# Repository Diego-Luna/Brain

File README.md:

# Brain 🧠

Brain(Cerebro) es una placa de desarrollo, que cuenta con un EEG (electroencefalograma) que mediante electrodos medimos la actividad cerebral de 12 Hz - 30 Hz, que corresponde a la concentración, con el objetivo de utilizarlo como una herramienta de aprendizaje en distintas disciplinas que se puede llevar a cualquier parte para aprender mientras te diviertes.
De igual manera se está desarrollando una plataforma para facilitar el uso y el aprendizaje con Brain.

## Desarrollo de placa

Este desarollo es una colaboracion con Electronic cats ([web](https://electroniccats.com))  y MoonMakers ([web](https://moonmakers.org/)) fue creada en la plataforma de Kicad 5.1

Usamos el microcontrolador nrf52840 en la forma E73-2G4M08S1C, está construido alrededor de la CPU ARM® Cortex ™ -M4 de 32 bits, tiene soporte de protocolo para Bluetooth 5, Bluetooth mesh, Thread, Zigbee, 802.15.4, ANT y pilas propietarias de 2.4 GHz. también tienen una resolución de 12 bits en puertos analogicos.

En la parte de los filtros EEG usamos el chip ads1294, cuenta con una resolución de 24 bits por canal, y hasta con 4 canales disponibles que pueden también usarse como un ECG (electrocardiograma)

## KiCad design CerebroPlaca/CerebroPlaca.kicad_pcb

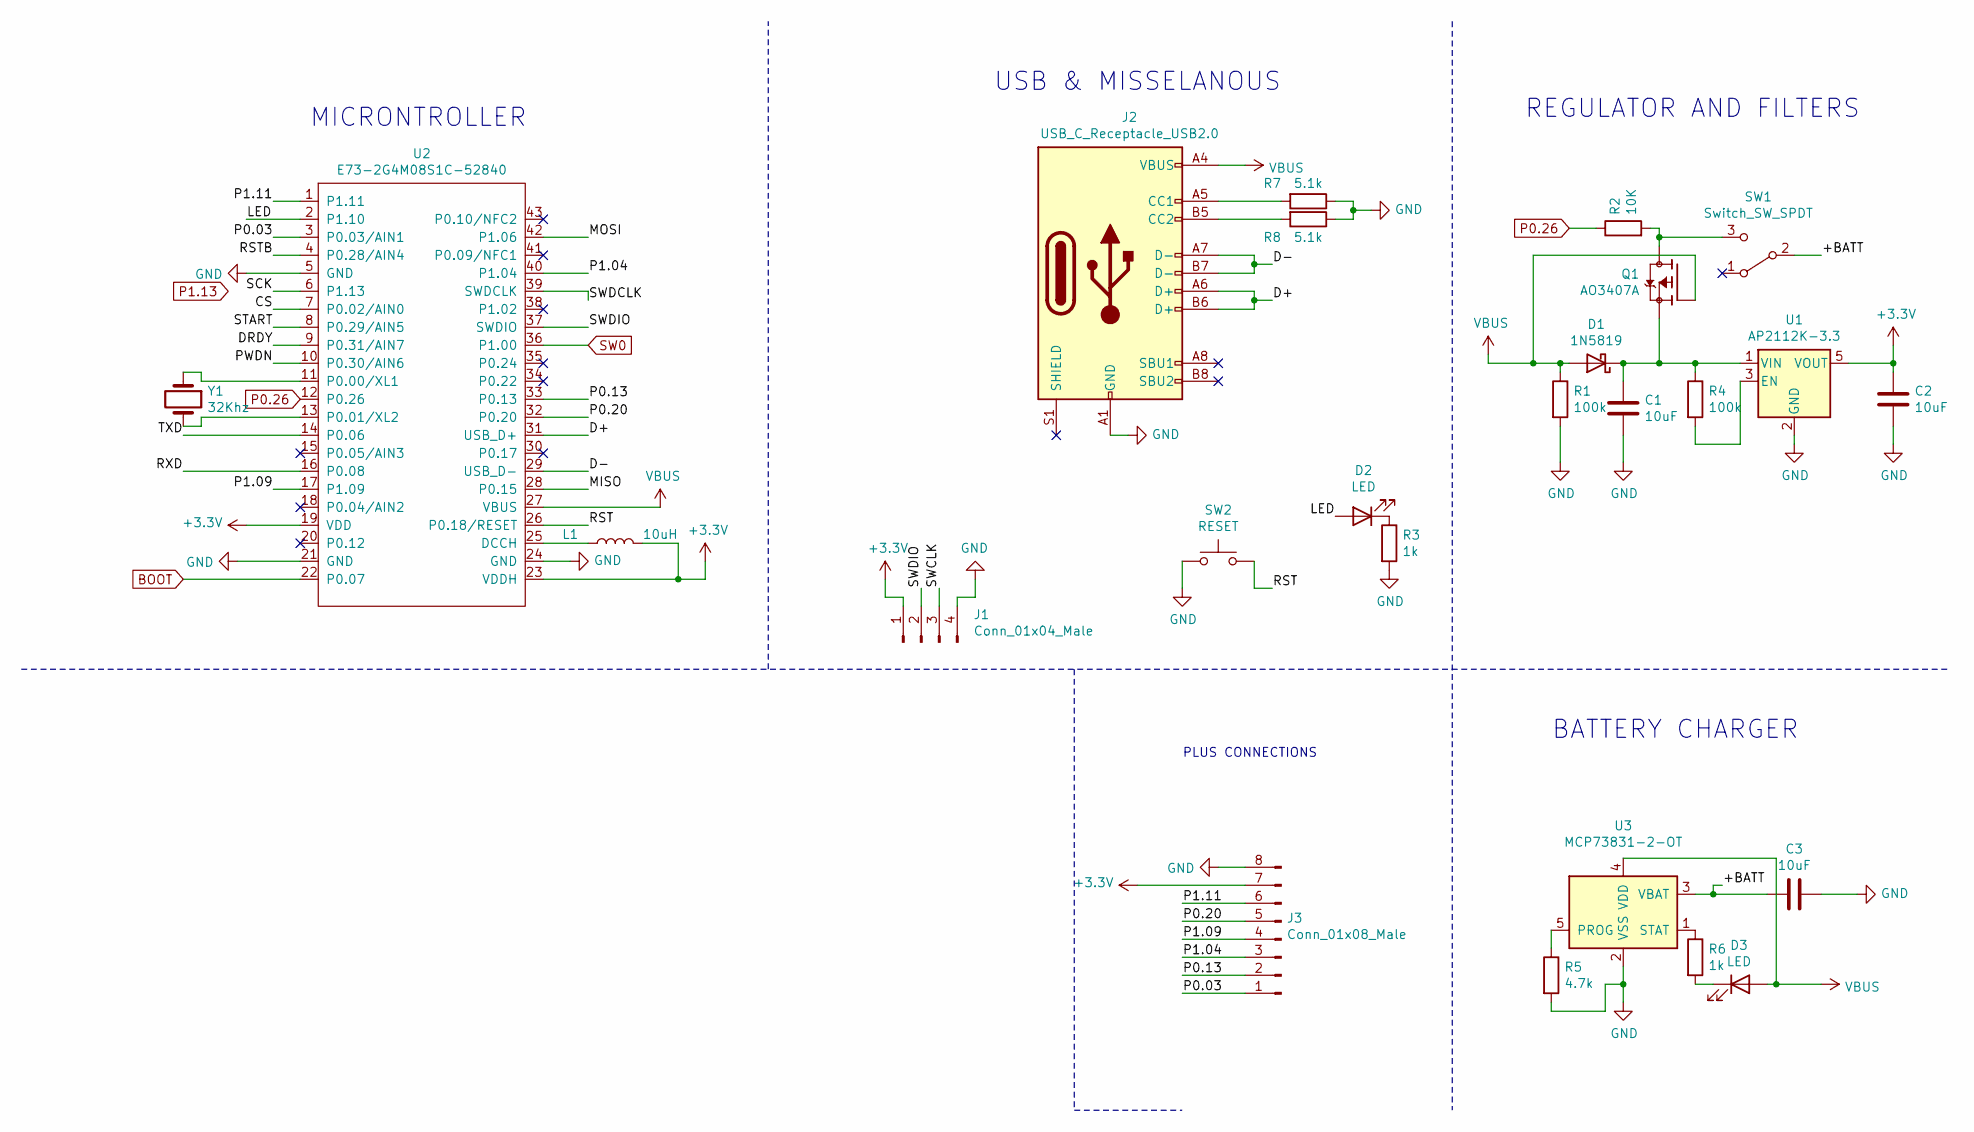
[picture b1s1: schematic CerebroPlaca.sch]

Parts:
C1, C2, C3: 10uF; C_0805_2012Metric
D1: 1N5819; D_SOD-123F
D2, D3: LED; LED_0603_1608Metric
J1: Conn_01x04_Male; PinHeader_1x04_P1.00mm_Vertical
J2: USB_C_Receptacle_USB2.0; usb_type_c
J3: Conn_01x08_Male; coenctor_8-(4-4)
L1: 10uH; L_7.3x7.3_H3.5
Q1: AO3407A; SOT-23
R1, R4: 100k; R_0603_1608Metric
R2: 10K; R_0603_1608Metric
R3, R6: 1k; R_0603_1608Metric
R5: 4.7k; R_0603_1608Metric
R7, R8: 5.1k; R_0603_1608Metric
SW1: Switch_SW_SPDT; switch_MSK-12C02_smd
SW2: RESET; SW_SPST_TL3342
U1: AP2112K-3.3; SOT-23-5
U2: E73-2G4M08S1C-52840; E73-2G4M08S1C
U3: MCP73831-2-OT; SOT-23-5
Y1: 32Khz; Crystal_Round_D1.0mm_Vertical

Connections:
+3V3: C2.1, J1.1, J3.7, L1.2, U1.5 (VOUT), U2.19 (VDD), U2.23 (VDDH)
/+BATT: C3.2, SW1.2 (B), U3.3 (VBAT)
/CS: U2.7 (P0.02/AIN0)
/D+: J2.A6 (D+), J2.B6 (D+), U2.31 (USB_D+)
/D-: J2.A7 (D-), J2.B7 (D-), U2.29 (USB_D-)
/DRDY: U2.9 (P0.31/AIN7)
/LED: D2.2 (A), U2.2 (P1.10)
/MISO: U2.28 (P0.15)
/MOSI: U2.42 (P1.06)
/P0.03: J3.1, U2.3 (P0.03/AIN1)
/P0.13: J3.2, U2.33 (P0.13)
/P0.20: J3.5, U2.32 (P0.20)
/P1.04: J3.3, U2.40 (P1.04)
/P1.09: J3.4, U2.17 (P1.09)
/P1.11: J3.6, U2.1 (P1.11)
/PWDN: U2.10 (P0.30/AIN6)
/RST: SW2.3 (B), SW2.4 (B), U2.26 (P0.18/RESET)
/RSTB: U2.4 (P0.28/AIN4)
/RXD: U2.16 (P0.08)
/SCK: U2.6 (P1.13)
/START: U2.8 (P0.29/AIN5)
/SWCLK: J1.3
/SWDCLK: U2.39 (SWDCLK)
/SWDIO: J1.2, U2.37 (SWDIO)
/TXD: U2.14 (P0.06)
BOOT: U2.22 (P0.07)
GND: C1.2, C2.2, C3.1, J1.4, J2.A1 (GND), J2.A12 (GND), J2.B1 (GND), J2.B12 (GND), J3.8, R1.2, R3.2, R5.2, R7.1, R8.1, SW2.1 (A), SW2.2 (A), U1.2 (GND), U2.5 (GND), U2.21 (GND), U2.24 (GND), U3.2 (VSS)
unnamed: C1.1, D1.1 (K), Q1.2 (S), R4.1, U1.1 (VIN)
unnamed: D2.1 (K), R3.1
unnamed: D3.1 (K), R6.2
unnamed: J2.A5 (CC1), R7.2
unnamed: J2.B5 (CC2), R8.2
unnamed: L1.1, U2.25 (DCCH)
unnamed: Q1.3 (D), R2.2, SW1.3 (C)
unnamed: R4.2, U1.3 (EN)
unnamed: R5.1, U3.5 (PROG)
unnamed: R6.1, U3.1 (STAT)
unnamed: U2.11 (P0.00/XL1), Y1.1
unnamed: U2.13 (P0.01/XL2), Y1.2
P0.26: R2.1, U2.12 (P0.26)
SW0: U2.36 (P1.00)
VBUS: D1.2 (A), D3.2 (A), J2.A4 (VBUS), J2.A9 (VBUS), J2.B4 (VBUS), J2.B9 (VBUS), Q1.1 (G), R1.1, U2.27 (VBUS), U3.4 (VDD)

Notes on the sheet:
MICRONTROLLER
USB & MISSELANOUS
REGULATOR AND FILTERS
BATTERY CHARGER
PLUS CONNECTIONS

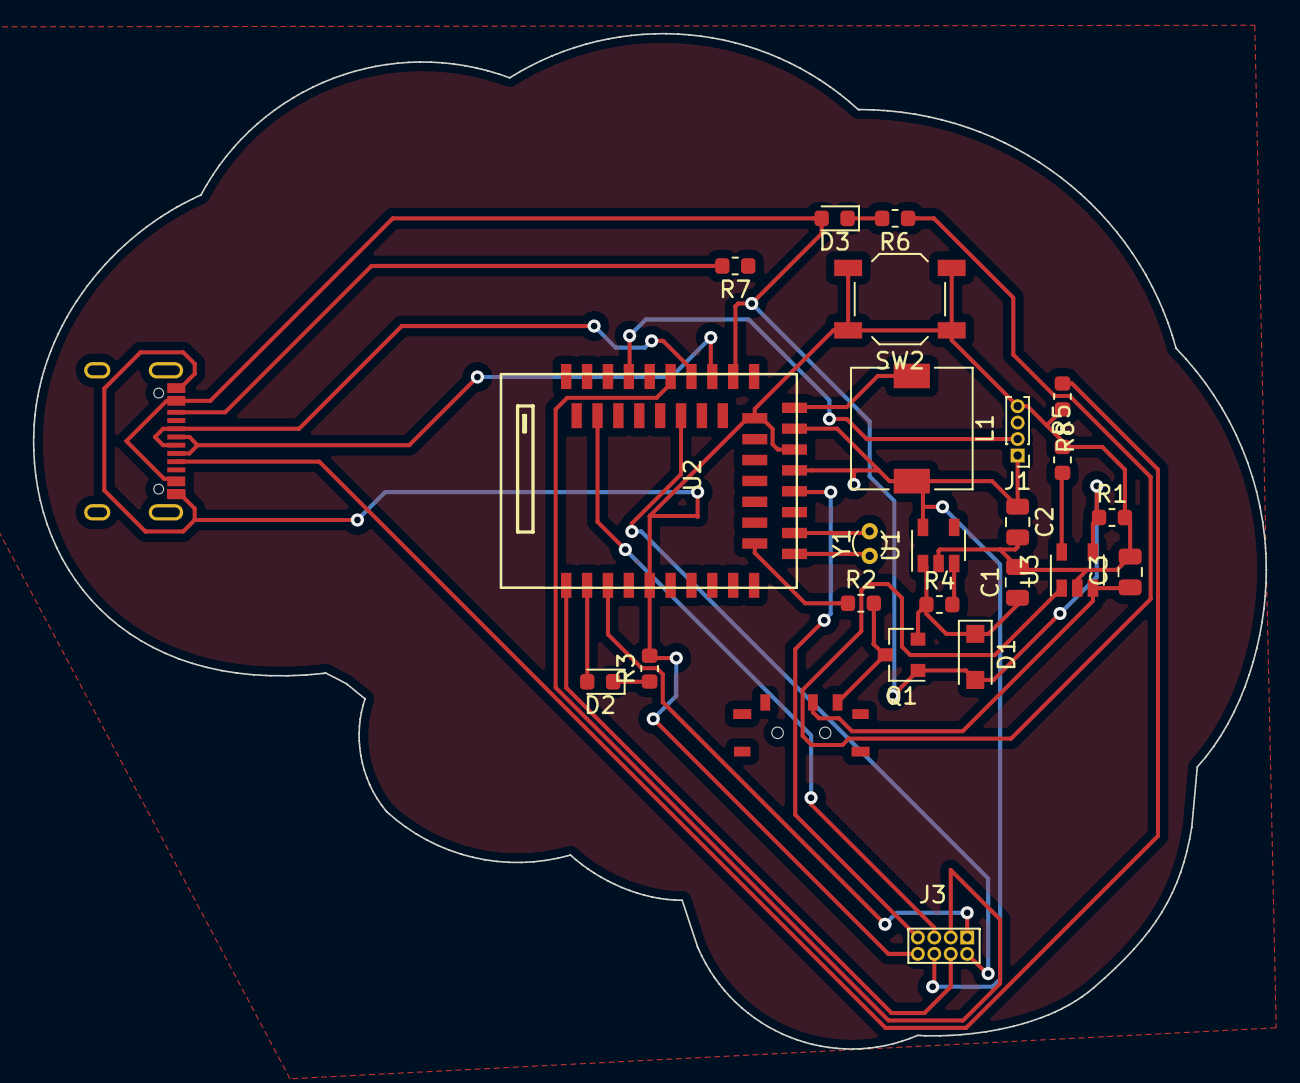
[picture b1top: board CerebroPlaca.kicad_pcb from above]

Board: 2 copper layers, 75.0 x 61.8 mm, 26 parts (0 on the bottom side), 27 nets.

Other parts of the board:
Ref**: Val**; CerebroInkscape

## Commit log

2020-02-24 iniciando proyecto
2020-02-26 se queda con el USB-C
2020-02-28 Cambio de esquemático en placa cerebro, con prueba de placa de la mima carpeta
2020-03-01 Reconfig schematic
2020-03-01 Fix GND and PWR Reset Resistor
2020-03-03 ajustes en placaCerebro
2020-03-03 iniciando
2020-03-03 el esquematico esta casi listo, solo falta la footprin del ads1294
2020-03-04 resize 7.5cm for shezen2kicad
2020-03-05 Tanto esquematico como pcb, preparados
2020-03-05 ajuste de la placa a 7.5 cm de ancho
2020-03-05 ajusted de placa
2020-03-12 Agregando README
